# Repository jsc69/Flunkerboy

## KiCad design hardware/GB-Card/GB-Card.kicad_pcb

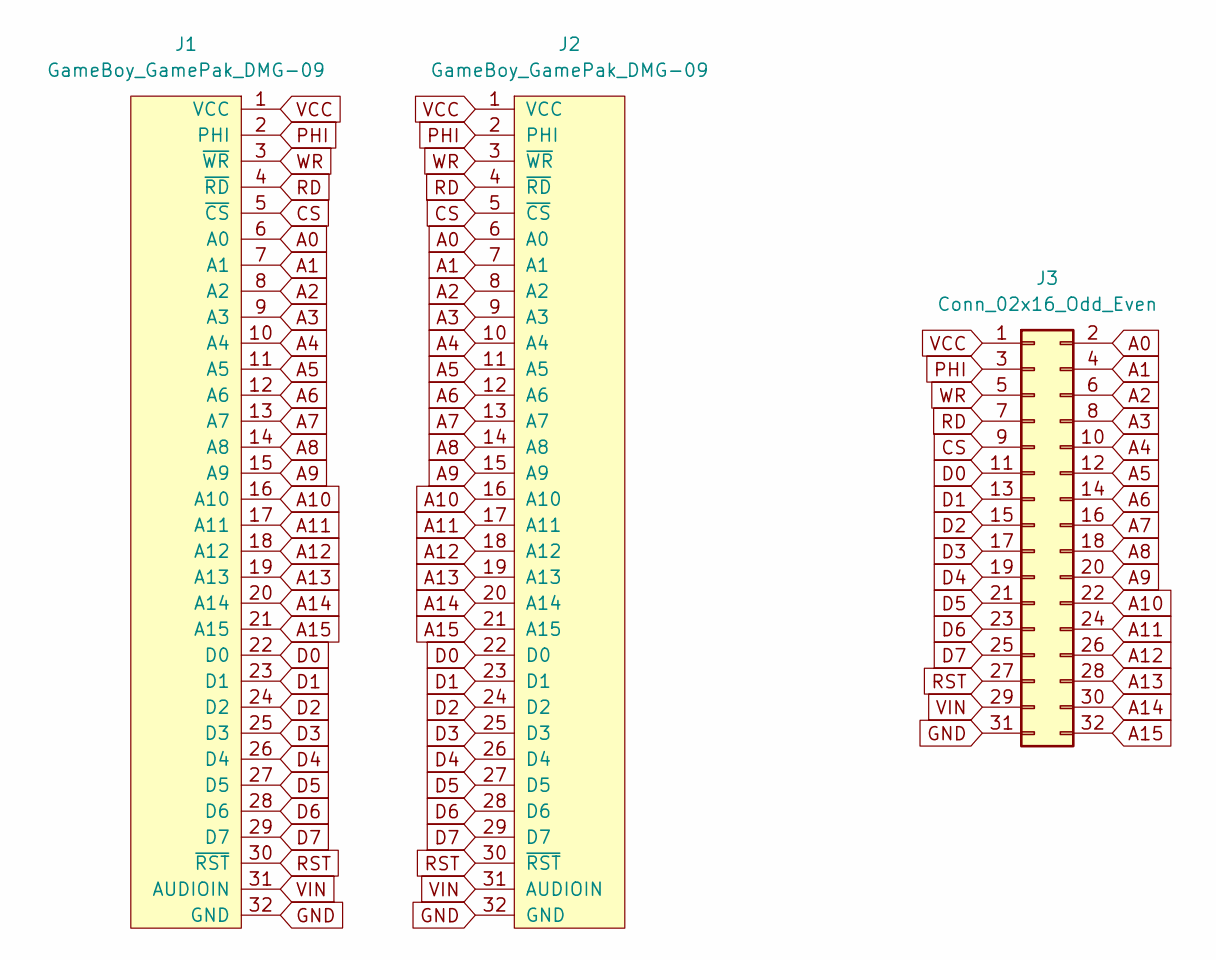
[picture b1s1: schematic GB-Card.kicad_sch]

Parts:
J1: GameBoy_GamePak_DMG-09; GameBoy_GamePak_DMG-09_P1.50mm_Edge
J2: GameBoy_GamePak_DMG-09; GB_GBC_1x32
J3: Conn_02x16_Odd_Even; PinHeader_2x16_P2.54mm_Vertical_SMD

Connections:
A0: J1.6 (A0), J2.6 (A0), J3.2
A1: J1.7 (A1), J2.7 (A1), J3.4
A2: J1.8 (A2), J2.8 (A2), J3.6
A3: J1.9 (A3), J2.9 (A3), J3.8
A4: J1.10 (A4), J2.10 (A4), J3.10
A5: J1.11 (A5), J2.11 (A5), J3.12
A6: J1.12 (A6), J2.12 (A6), J3.14
A7: J1.13 (A7), J2.13 (A7), J3.16
A8: J1.14 (A8), J2.14 (A8), J3.18
A9: J1.15 (A9), J2.15 (A9), J3.20
A10: J1.16 (A10), J2.16 (A10), J3.22
A11: J1.17 (A11), J2.17 (A11), J3.24
A12: J1.18 (A12), J2.18 (A12), J3.26
A13: J1.19 (A13), J2.19 (A13), J3.28
A14: J1.20 (A14), J2.20 (A14), J3.30
A15: J1.21 (A15), J2.21 (A15), J3.32
CS: J1.5 (~CS), J2.5 (~CS), J3.9
D0: J1.22 (D0), J2.22 (D0), J3.11
D1: J1.23 (D1), J2.23 (D1), J3.13
D2: J1.24 (D2), J2.24 (D2), J3.15
D3: J1.25 (D3), J2.25 (D3), J3.17
D4: J1.26 (D4), J2.26 (D4), J3.19
D5: J1.27 (D5), J2.27 (D5), J3.21
D6: J1.28 (D6), J2.28 (D6), J3.23
D7: J1.29 (D7), J2.29 (D7), J3.25
GND: J1.32 (GND), J2.32 (GND), J3.31
PHI: J1.2 (PHI), J2.2 (PHI), J3.3
RD: J1.4 (~RD), J2.4 (~RD), J3.7
RST: J1.30 (~RST), J2.30 (~RST), J3.27
VCC: J1.1 (VCC), J2.1 (VCC), J3.1
VIN: J1.31 (AUDIOIN), J2.31 (AUDIOIN), J3.29
WR: J1.3 (~WR), J2.3 (~WR), J3.5

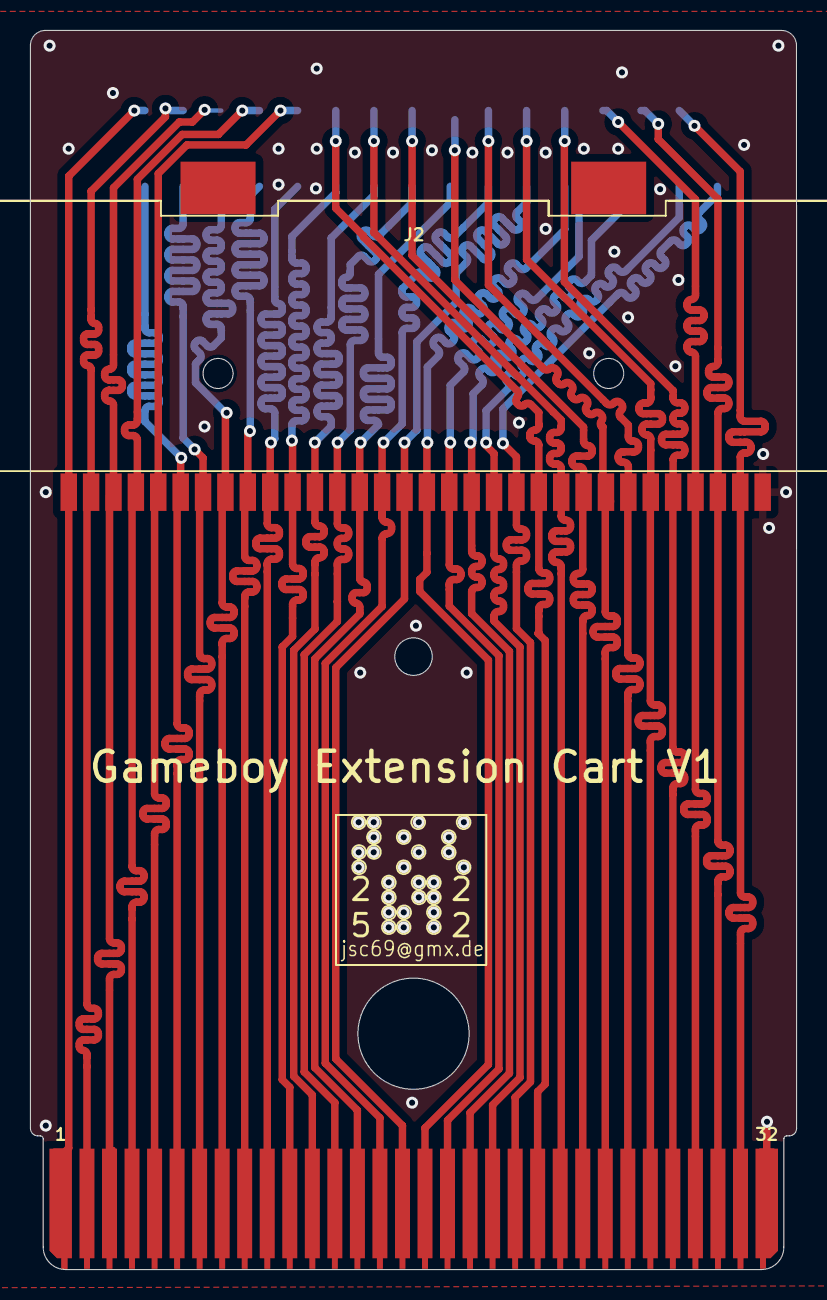
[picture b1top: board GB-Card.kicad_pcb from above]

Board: 2 copper layers, 51.0 x 82.5 mm, 3 parts (1 on the bottom side), 32 nets.

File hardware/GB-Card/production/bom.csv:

Designator,Footprint,Quantity,Value,LCSC Part #
J1,GameBoy_GamePak_DMG-09_P1.50mm_Edge,1,GameBoy_GamePak_DMG-09,
J2,GB_GBC_1x32,1,GameBoy_GamePak_DMG-09,
J3,PinHeader_2x16_P2.54mm_Vertical_SMD,1,Conn_02x16_Odd_Even,

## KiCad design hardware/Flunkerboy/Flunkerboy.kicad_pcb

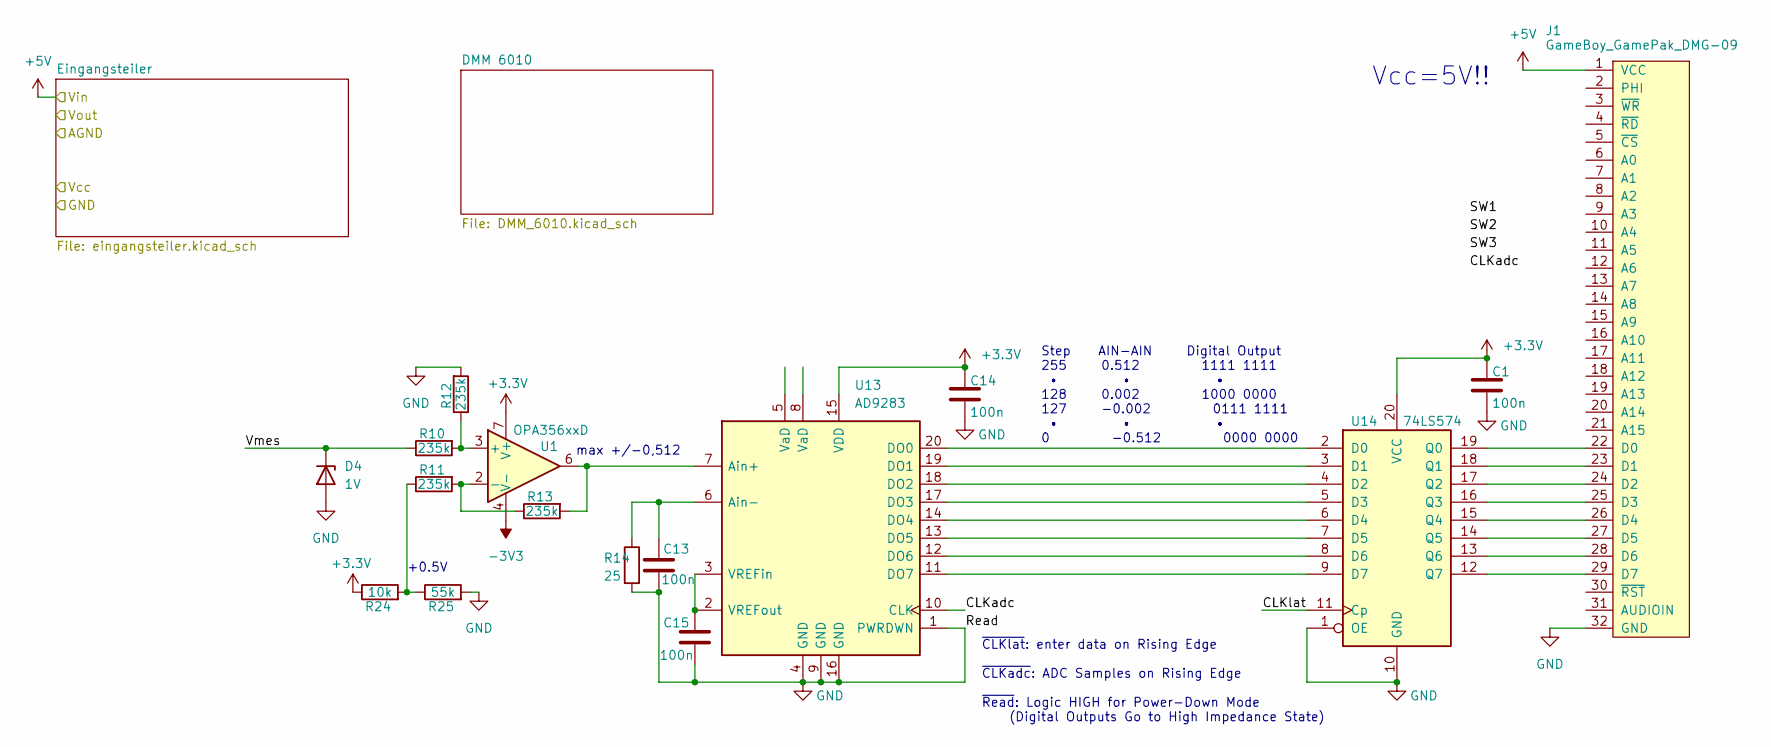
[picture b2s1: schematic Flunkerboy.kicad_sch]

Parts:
C1, C13, C14, C15: 100n; C_0603_1608Metric; LCSC part C69335
D4: 1V; D_SOD-123F
J1: GameBoy_GamePak_DMG-09; GameBoy_GamePak_DMG-09_P1.50mm_Edge
R10, R11, R12, R13: 235k; R_0805_2012Metric_Pad1.20x1.40mm_HandSolder
R14: 25; R_0805_2012Metric_Pad1.20x1.40mm_HandSolder
R24: 10k; R_0805_2012Metric_Pad1.20x1.40mm_HandSolder
R25: 55k; R_0805_2012Metric_Pad1.20x1.40mm_HandSolder
U1: OPA356xxD; SOIC-8_3.9x4.9mm_P1.27mm
U13: AD9283; SSOP-20_5.3x7.2mm_P0.65mm; LCSC part C653448
U14: 74LS574; SOIC-20W_7.5x15.4mm_P1.27mm

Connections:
+3.3V: C1.1, C14.1, R24.1, U1.7 (V+), U13.15 (VDD), U14.20 (VCC)
+5V: J1.1 (VCC); also elsewhere on the board
-3V3: U1.4 (V-); also elsewhere on the board
/CLKadc: U13.10 (CLK)
/CLKlat: U14.11 (Cp)
/Vmes: D4.1 (K), R10.1
GND: C1.2, C13.2, C14.2, C15.2, D4.2 (A), J1.32 (GND), R12.2, R14.2, R25.2, U13.1 (PWRDWN), U13.4 (GND), U13.9 (GND), U13.16 (GND), U14.1 (OE), U14.10 (GND); also elsewhere on the board
unnamed: J1.22 (D0), U14.19 (Q0)
unnamed: J1.23 (D1), U14.18 (Q1)
unnamed: J1.24 (D2), U14.17 (Q2)
unnamed: J1.25 (D3), U14.16 (Q3)
unnamed: J1.26 (D4), U14.15 (Q4)
unnamed: J1.27 (D5), U14.14 (Q5)
unnamed: J1.28 (D6), U14.13 (Q6)
unnamed: J1.29 (D7), U14.12 (Q7)
unnamed: R11.1, R24.2, R25.1
unnamed: R10.2, R12.1, U1.3 (+)
unnamed: R11.2, R13.1, U1.2 (-)
unnamed: R13.2, U1.6, U13.7 (Ain+)
unnamed: C13.1, R14.1, U13.6 (Ain-)
unnamed: U13.20 (DO0), U14.2 (D0)
unnamed: U13.19 (DO1), U14.3 (D1)
unnamed: U13.18 (DO2), U14.4 (D2)
unnamed: U13.17 (DO3), U14.5 (D3)
unnamed: U13.14 (DO4), U14.6 (D4)
unnamed: U13.13 (DO5), U14.7 (D5)
unnamed: U13.12 (DO6), U14.8 (D6)
unnamed: U13.11 (DO7), U14.9 (D7)
unnamed: C15.1, U13.2 (VREFout), U13.3 (VREFin)

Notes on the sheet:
~{CLKlat}: enter data on Rising Edge ~{CLKadc}: ADC Samples on Rising Edge ~{Read}: Logic HIGH for Power-Down Mode (Digital Outputs Go to High Impedance State)
max +/-0,512
Step AIN-AIN Digital Output 255 0.512 1111 1111 • • • 128 0.002 1000 0000 127 -0.002 0111 1111 • • • 0 -0.512 0000 0000
Vcc=5V!!
+0.5V

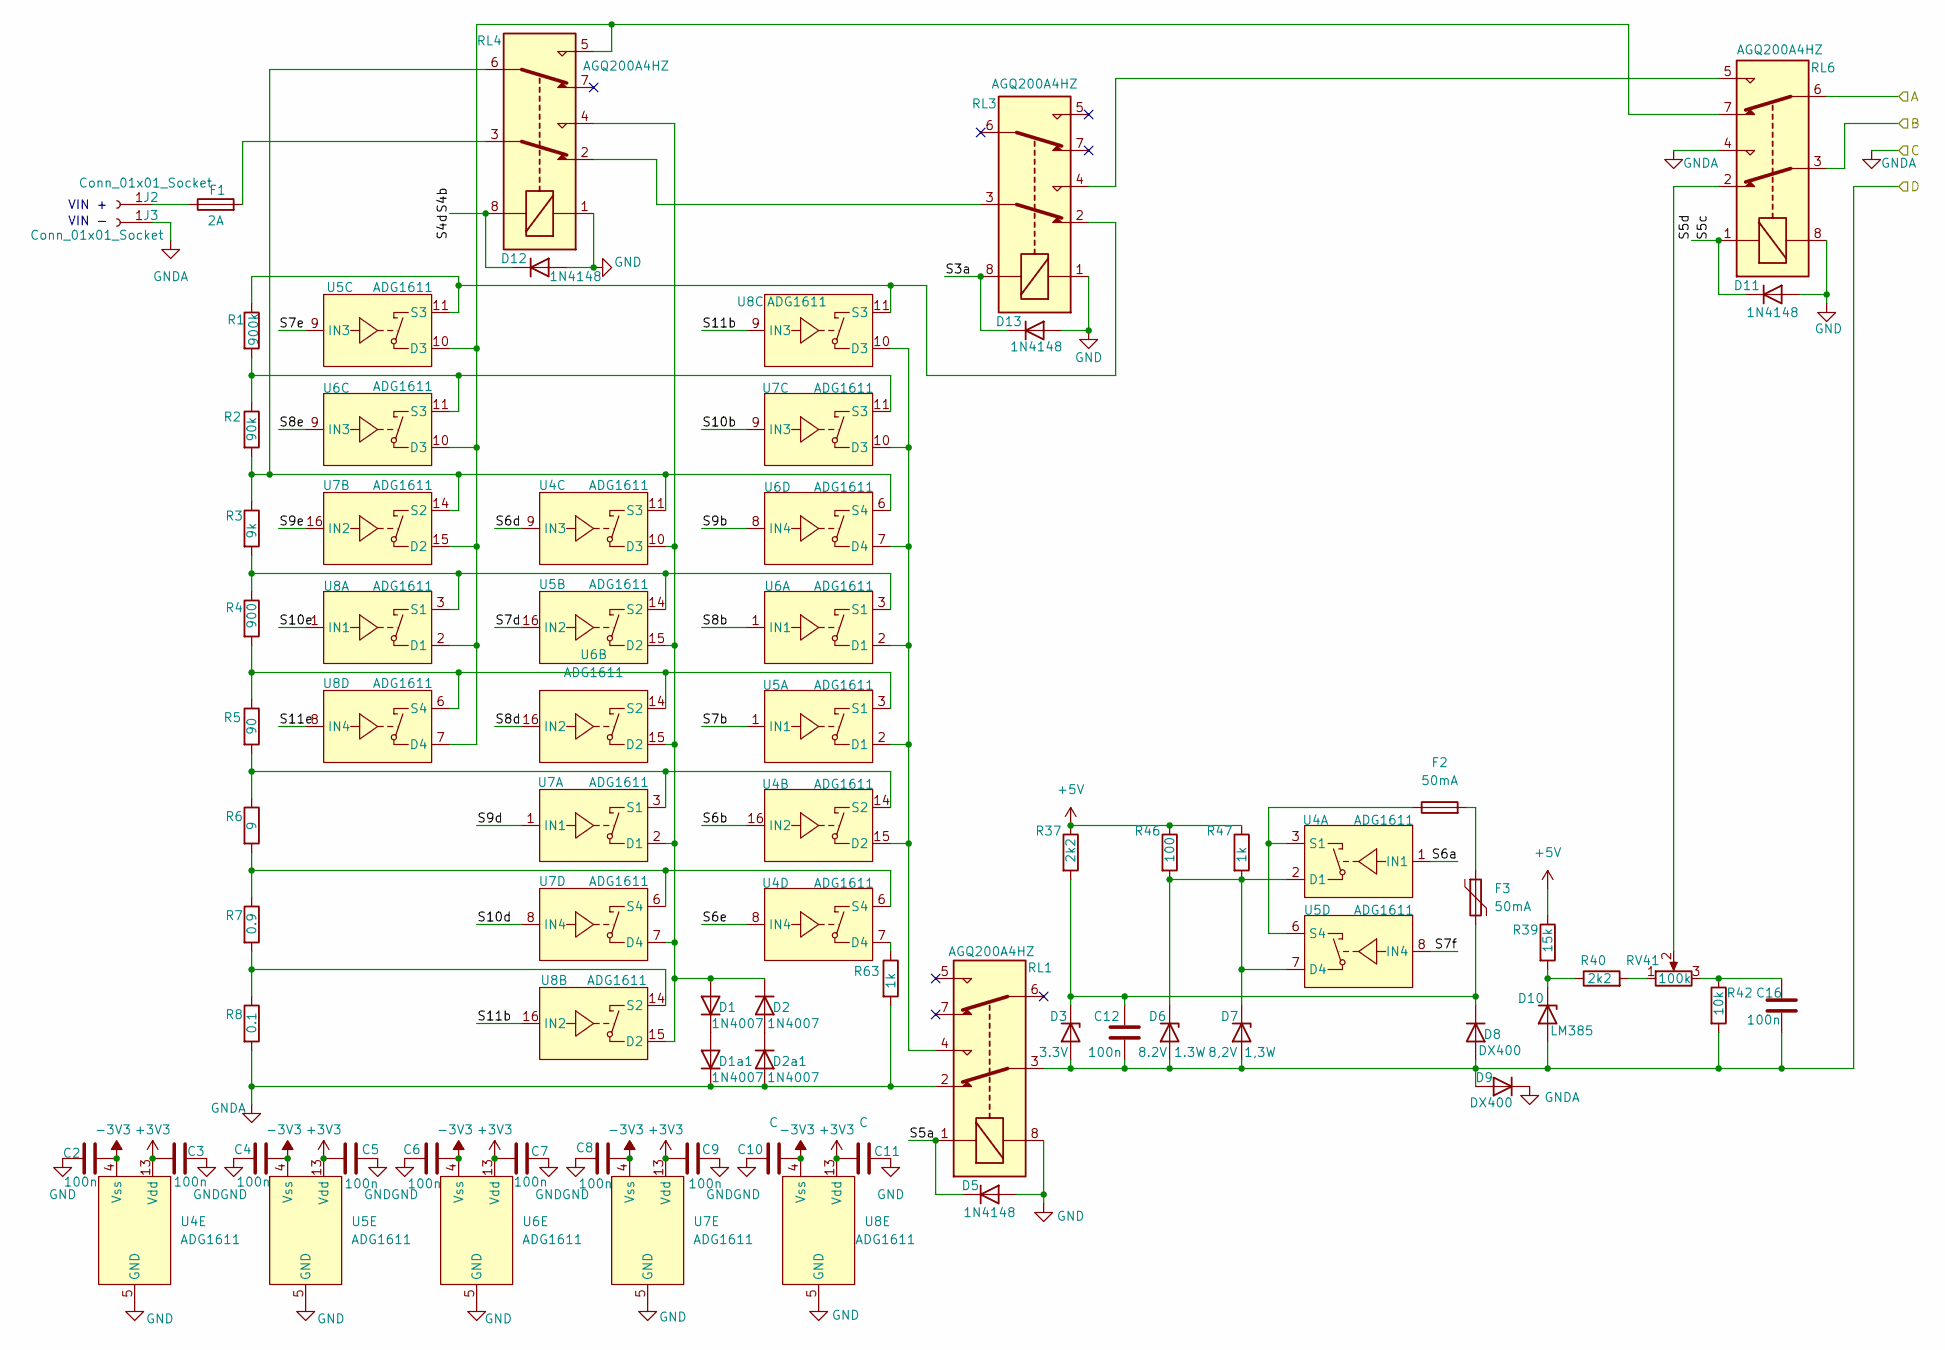
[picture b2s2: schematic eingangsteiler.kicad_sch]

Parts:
C2, C3, C4, C5, C6, C7, C8, C9, C12, C16: 100n; C_0805_2012Metric
C10, C11: C; C_0805_2012Metric
D1, D1a1, D2, D2a1: 1N4007; D_SOD-123F
D3: 3.3V; D_SOD-123
D5, D11, D12, D13: 1N4148; D_SOD-123
D6: 8.2V 1.3W; D_SMB
D7: 8,2V 1,3W; D_SMB
D8, D9: DX400; D_SOD-123
D10: LM385; SOT-23
F1: 2A; 2410
F2, F3: 50mA; R_0805_2012Metric
J2, J3: Conn_01x01_Socket; Banana_Cliff_FCR7350B_S16N-PC_Horizontal
R1: 900k; R_0805_2012Metric
R2: 90k; R_0805_2012Metric
R3: 9k; R_0805_2012Metric
R4: 900; R_0805_2012Metric
R5: 90; R_0805_2012Metric
R6: 9; R_0805_2012Metric
R7: 0.9; R_0805_2012Metric
R8: 0.1; R_0805_2012Metric
R37, R40: 2k2; R_0805_2012Metric
R39: 15k; R_0805_2012Metric
R42: 10k; R_0805_2012Metric
R46: 100; R_0805_2012Metric
R47, R63: 1k; R_0805_2012Metric
RL1, RL3, RL4, RL6: AGQ200A4HZ; Relay_DPDT_Omron_G6K-2P-Y
RV41: 100k; Potentiometer_Bourns_3224J_Horizontal
U4, U5, U6, U7, U8: ADG1611; TSSOP-16_4.4x5mm_P0.65mm; LCSC part C377682

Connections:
+3V3: C3.2, C5.2, C7.2, C9.2, C11.2, U4.13 (Vdd), U5.13 (Vdd), U6.13 (Vdd), U7.13 (Vdd), U8.13 (Vdd)
+5V: R37.1, R39.1, R46.1, R47.1; also elsewhere on the board
-3V3: C2.1, C4.1, C6.1, C8.1, C10.1, U4.4 (Vss), U5.4 (Vss), U6.4 (Vss), U7.4 (Vss), U8.4 (Vss); also elsewhere on the board
/Eingangsteiler/A: RL6.6
/Eingangsteiler/B: RL6.3
/Eingangsteiler/D: C12.2, C16.2, D3.2 (A), D6.2 (A), D7.2 (A), D8.2 (A), D9.2 (A), D10.2 (A), R42.2, RL1.3
/Eingangsteiler/S3a: D13.1 (K), RL3.8
/Eingangsteiler/S4b: D12.1 (K), RL4.8
/Eingangsteiler/S5a: D5.1 (K), RL1.1
/Eingangsteiler/S5c: D11.1 (K), RL6.1
/Eingangsteiler/S6a: U4.1 (IN1)
/Eingangsteiler/S6b: U4.16 (IN2)
/Eingangsteiler/S6d: U4.9 (IN3)
/Eingangsteiler/S6e: U4.8 (IN4)
/Eingangsteiler/S7b: U5.1 (IN1)
/Eingangsteiler/S7d: U5.16 (IN2)
/Eingangsteiler/S7e: U5.9 (IN3)
/Eingangsteiler/S7f: U5.8 (IN4)
/Eingangsteiler/S8b: U6.1 (IN1)
/Eingangsteiler/S8d: U6.16 (IN2)
/Eingangsteiler/S8e: U6.9 (IN3)
/Eingangsteiler/S9b: U6.8 (IN4)
/Eingangsteiler/S9d: U7.1 (IN1)
/Eingangsteiler/S9e: U7.16 (IN2)
/Eingangsteiler/S10b: U7.9 (IN3)
/Eingangsteiler/S10d: U7.8 (IN4)
/Eingangsteiler/S10e: U8.1 (IN1)
/Eingangsteiler/S11b: U8.9 (IN3), U8.16 (IN2)
/Eingangsteiler/S11e: U8.8 (IN4)
GND: C2.2, C3.1, C4.2, C5.1, C6.2, C7.1, C8.2, C9.1, C10.2, C11.1, D5.2 (A), D11.2 (A), D12.2 (A), D13.2 (A), RL1.8, RL3.1, RL4.1, RL6.8, U4.5 (GND), U5.5 (GND), U6.5 (GND), U7.5 (GND), U8.5 (GND); also elsewhere on the board
GNDA: D1a1.1 (K), D2a1.2 (A), D9.1 (K), J3.1, R8.2, R63.2, RL1.2, RL6.4
unnamed: C16.1, R42.1, RV41.3
unnamed: D1.2 (A), D2.1 (K), RL4.4, U4.10 (D3), U5.15 (D2), U6.15 (D2), U7.2 (D1), U7.7 (D4), U8.15 (D2)
unnamed: D1.1 (K), D1a1.2 (A)
unnamed: D2.2 (A), D2a1.1 (K)
unnamed: C12.1, D3.1 (K), D8.1 (K), F3.2, R37.2
unnamed: D6.1 (K), D7.1 (K), R46.2, R47.2, U4.2 (D1), U5.7 (D4)
unnamed: D10.1 (K), R39.2, R40.1
unnamed: F1.2, RL4.3
unnamed: F2.2, F3.1
unnamed: F1.1, J2.1
unnamed: R40.2, RV41.1
unnamed: RL3.3, RL4.2
unnamed: RL3.4, RL6.5
unnamed: RL6.2, RV41.2
unnamed: F2.1, U4.3 (S1), U5.6 (S4)
unnamed: RL1.4, U4.15 (D2), U5.2 (D1), U6.2 (D1), U6.7 (D4), U7.10 (D3), U8.10 (D3)
unnamed: R5.2, R6.1, U4.14 (S2), U7.3 (S1)
unnamed: R2.2, R3.1, RL4.6, U4.11 (S3), U6.6 (S4), U7.14 (S2)
unnamed: R63.1, U4.7 (D4)
unnamed: R6.2, R7.1, U4.6 (S4), U7.6 (S4)
unnamed: R4.2, R5.1, U5.3 (S1), U6.14 (S2), U8.6 (S4)
unnamed: R3.2, R4.1, U5.14 (S2), U6.3 (S1), U8.3 (S1)
unnamed: RL4.5, RL6.7, U5.10 (D3), U6.10 (D3), U7.15 (D2), U8.2 (D1), U8.7 (D4)
unnamed: R1.1, RL3.2, U5.11 (S3), U8.11 (S3)
unnamed: R1.2, R2.1, U6.11 (S3), U7.11 (S3)
unnamed: R7.2, R8.1, U8.14 (S2)

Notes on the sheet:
VIN -
VIN +

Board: 2 copper layers, 72 parts (0 on the bottom side), 61 nets, no tracks yet.

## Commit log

2025-08-23 add mosfets
2025-08-23 backups ignored
2025-09-01 build imput devider
2025-09-19 add docs
2025-09-21 add 3D files
2026-01-10 add step model for gbc connector
